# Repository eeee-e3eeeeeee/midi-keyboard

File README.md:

# MIDI KEYBOARD

## Description 

A midi keyboard inspired by my favorite vocaloid voicebanks. : Miku, Adachi rei, and Kaai yuki. Has 3 buttons 6 touch pads, a rotary encoder and a slider.

### What does it do?

Its supposed to hook up the keyboard to a computer and use a software (for example: garage band) to make music with it.

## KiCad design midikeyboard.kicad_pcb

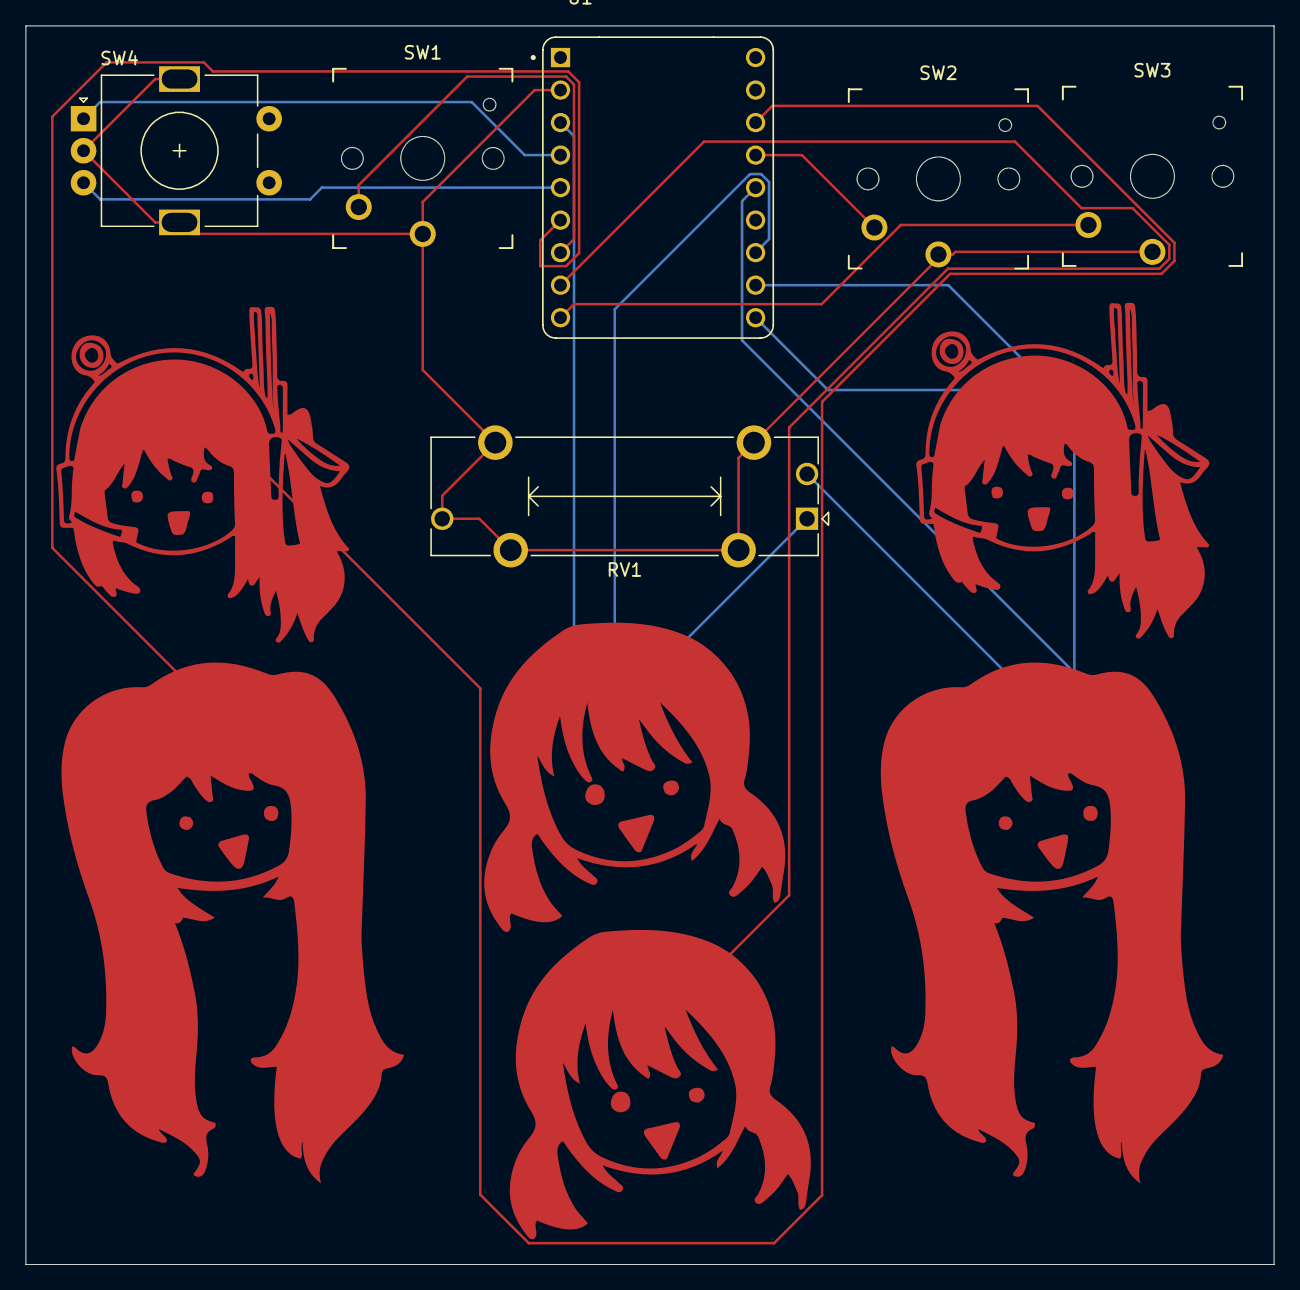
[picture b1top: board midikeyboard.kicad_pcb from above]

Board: 2 copper layers, 97.5 x 96.8 mm, 6 parts (0 on the bottom side), 8 nets.

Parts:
RV1: R_Potentiometer_MountingPin; Potentiometer_Bourns_PTA1543_Single_Slide
SW1, SW2, SW3: SW_Push; Kailh Choc Low-Profile Switches
SW4: RotaryEncoder_Switch_MP; RotaryEncoder_Alps_EC11E-Switch_Vertical_H20mm
U1: Waveshare ESP32-S3-ZERO; Waveshare ESP32-S3-Zero

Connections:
+3V3: RV1.1, U1.3V3 (3V3(OUT))
/button_1: SW1.2, U1.4 (GP4)
/button_2: SW2.2, U1.12 (GP12)
/button_3: SW3.2, U1.6 (GP6)
/enc_1: SW4.A, U1.1 (GP1)
/enc_2: SW4.B, U1.2 (GP2)
/slide_1: RV1.2, U1.8 (GP8)
GND: RV1.3, RV1.MP (MountPin), SW1.1, SW2.1, SW3.1, SW4.C, SW4.MP, U1.GND
